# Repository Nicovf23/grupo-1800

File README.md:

# grupo-DON JULIO 
Proyecto Carrito Don Julio
El proyecto Carrito Don Julio consiste en el diseño y desarrollo de un vehículo eléctrico a escala, controlado por radio (RC), orientado al automodelismo de competición en pista para adultos. El objetivo es construir un vehículo desde cero, con un diseño enfocado en el alto rendimiento, la precisión de conducción y las exigencias técnicas de las carreras RC.
El proyecto contempla el diseño y fabricación de un chasis propio, la integración de un sistema de propulsión 100 % eléctrico, el desarrollo de circuitos electrónicos con componentes SMD (Surface-Mount Device) y la implementación de sistemas de control. Cada elemento será diseñado y seleccionado considerando factores como la velocidad, la aceleración, la estabilidad, la distribución del peso y la eficiencia energética.
Para el diseño y desarrollo se utilizarán herramientas especializadas como FreeCAD, para el modelado tridimensional del chasis y sus componentes mecánicos; KiCad, para el diseño de esquemáticos y placas de circuito impreso; Qucs-S, para la simulación y el análisis de circuitos electrónicos; y OpenModelica, para el modelado y la simulación de sistemas dinámicos.
El enfoque principal será desarrollar un vehículo competitivo para carreras en circuitos de pista, aplicando principios de ingeniería mecánica, electrónica, programación y microcontroladores. Se buscará optimizar cada componente para obtener un equilibrio entre potencia, control, estabilidad y rendimiento, mediante un proceso continuo de diseño, fabricación, pruebas y ajustes.

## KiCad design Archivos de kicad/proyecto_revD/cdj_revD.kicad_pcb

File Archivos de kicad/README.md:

# Carrito Don Julio: placa principal (KiCad)

> ⚠️ **ESTADO: EN DESARROLLO. NO ES UNA VERSIÓN DE PRODUCCIÓN.**
> El ruteo está completo (DRC: 0 errores, 0 conexiones sin rutear), pero no mandar a fabricar todavía: faltan verificaciones físicas y una revisión del diseño (ver [AUDITORIA.md](AUDITORIA.md)).

**Revisión:** D, ruteo 3 (11 de noviembre de 2026)
**Herramienta:** KiCad 9.0
**Vehículo:** RC 1:7, 4WD, batería LiPo 6S (22.2 V nominal / 25.2 V cargada)

## Qué hace esta placa

| Bloque | Componentes principales |
|---|---|
| Microcontrolador | ESP32 DevKit V1 (DOIT, 30 pines) en zócalo |
| Sensor de movimiento | IMU LSM6DSL (I2C, dirección 0x6A) |
| Carga de batería por USB-C | CH224K (pide 20 V por PD) → BQ25756 (buck-boost 6S) |
| Monitoreo y balanceo de celdas | BQ76930 (6 celdas, por el cable de balanceo) |
| Alimentación 3.3 V | AP63203WU (componente recomendado por el profesor) |
| Luces | 2× BTS723GW (4 canales con diagnóstico) |
| Radio control | Entradas PWM ×3 + serie (CRSF/SBUS/iBUS), protegidas |
| Salidas | ESC y servo con buffer y habilitación |
| Protección | ESD5Z3.3T, SMF24CA/SMF26CA, SMF3.3, MBRA340T, fusible |

## Estructura de la carpeta

| Carpeta | Contenido |
|---|---|
| `proyecto_revD/` | Proyecto KiCad editable: esquemático, PCB, librería propia `CDJ` (símbolos y huellas) |
| `fabricacion_PRELIMINAR/` | Gerbers, taladros, BOM, posiciones (CPL) y modelo STEP. **Preliminares, no fabricar** |
| `documentacion/` | Esquemático en PDF, vista 3D, BOM clasificada (A/B/C), mapa de pines del DevKit, instrucciones y `EXPLICACION_PLACA.md` (qué hace cada componente y cada parte del PCB) |
| `reportes/` | Informes ERC, DRC y verificación de la netlist |
| `AUDITORIA.md` | Qué está verificado, qué no, y qué falta para producción |
| `NOTAS_DISENO.md` | Decisiones de diseño, supuestos y cálculos |

## Cómo abrir

1. Abrir `proyecto_revD/cdj_revD.kicad_pro` con KiCad 9.
2. La librería `CDJ` se carga sola desde la carpeta del proyecto (`sym-lib-table` y `fp-lib-table`).

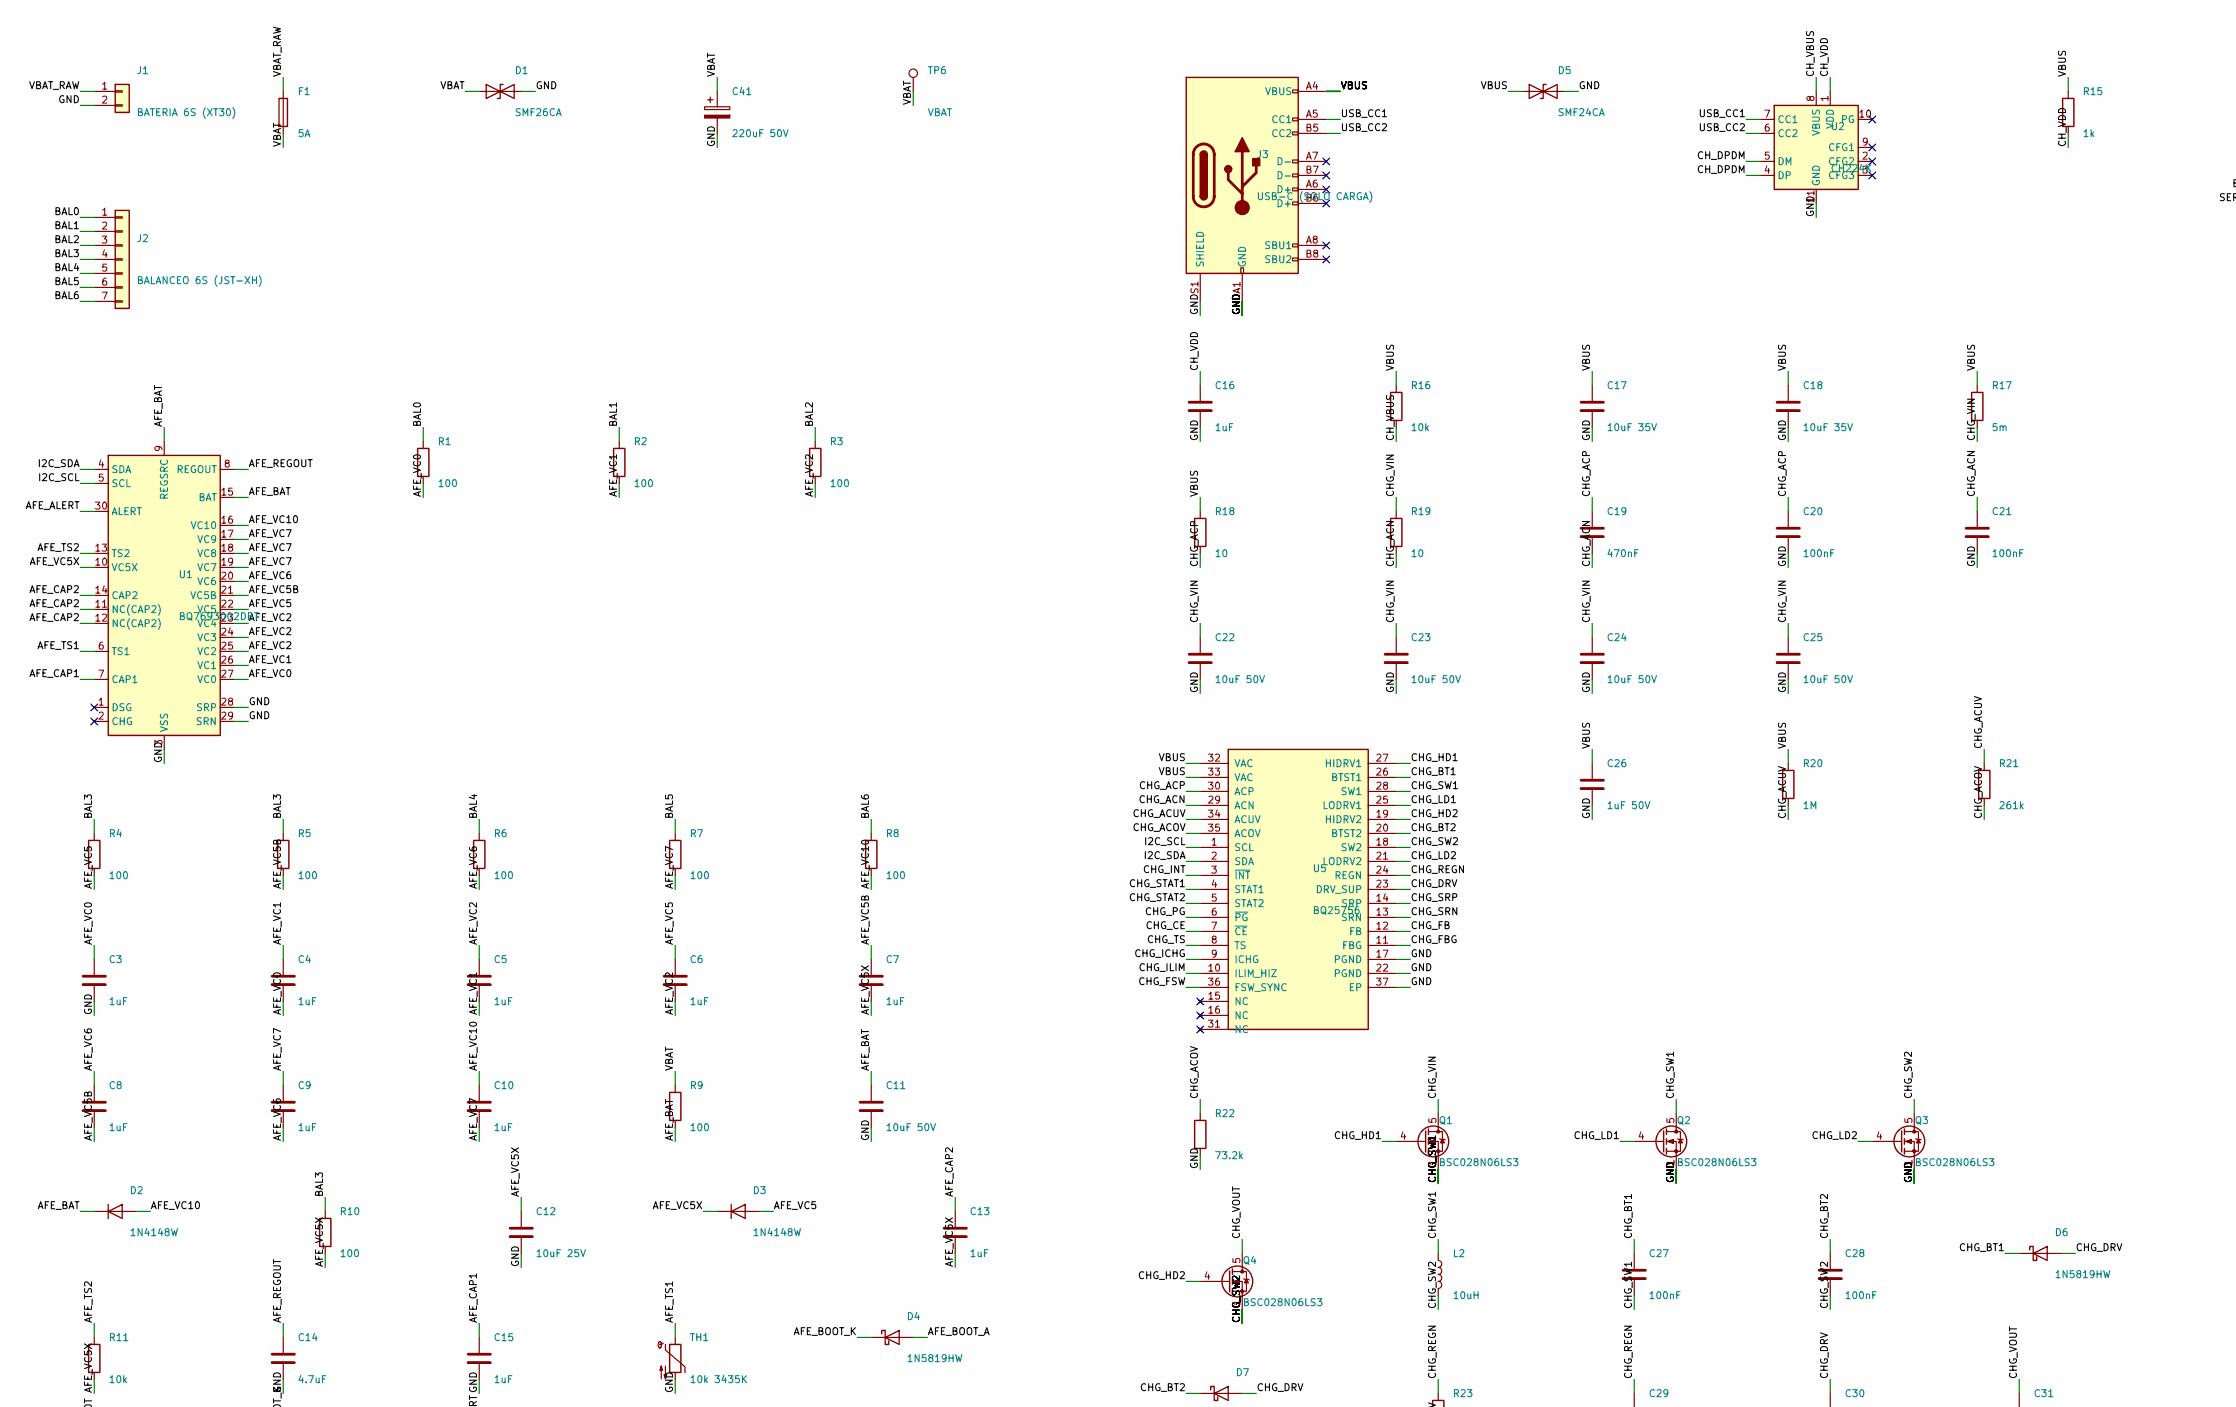
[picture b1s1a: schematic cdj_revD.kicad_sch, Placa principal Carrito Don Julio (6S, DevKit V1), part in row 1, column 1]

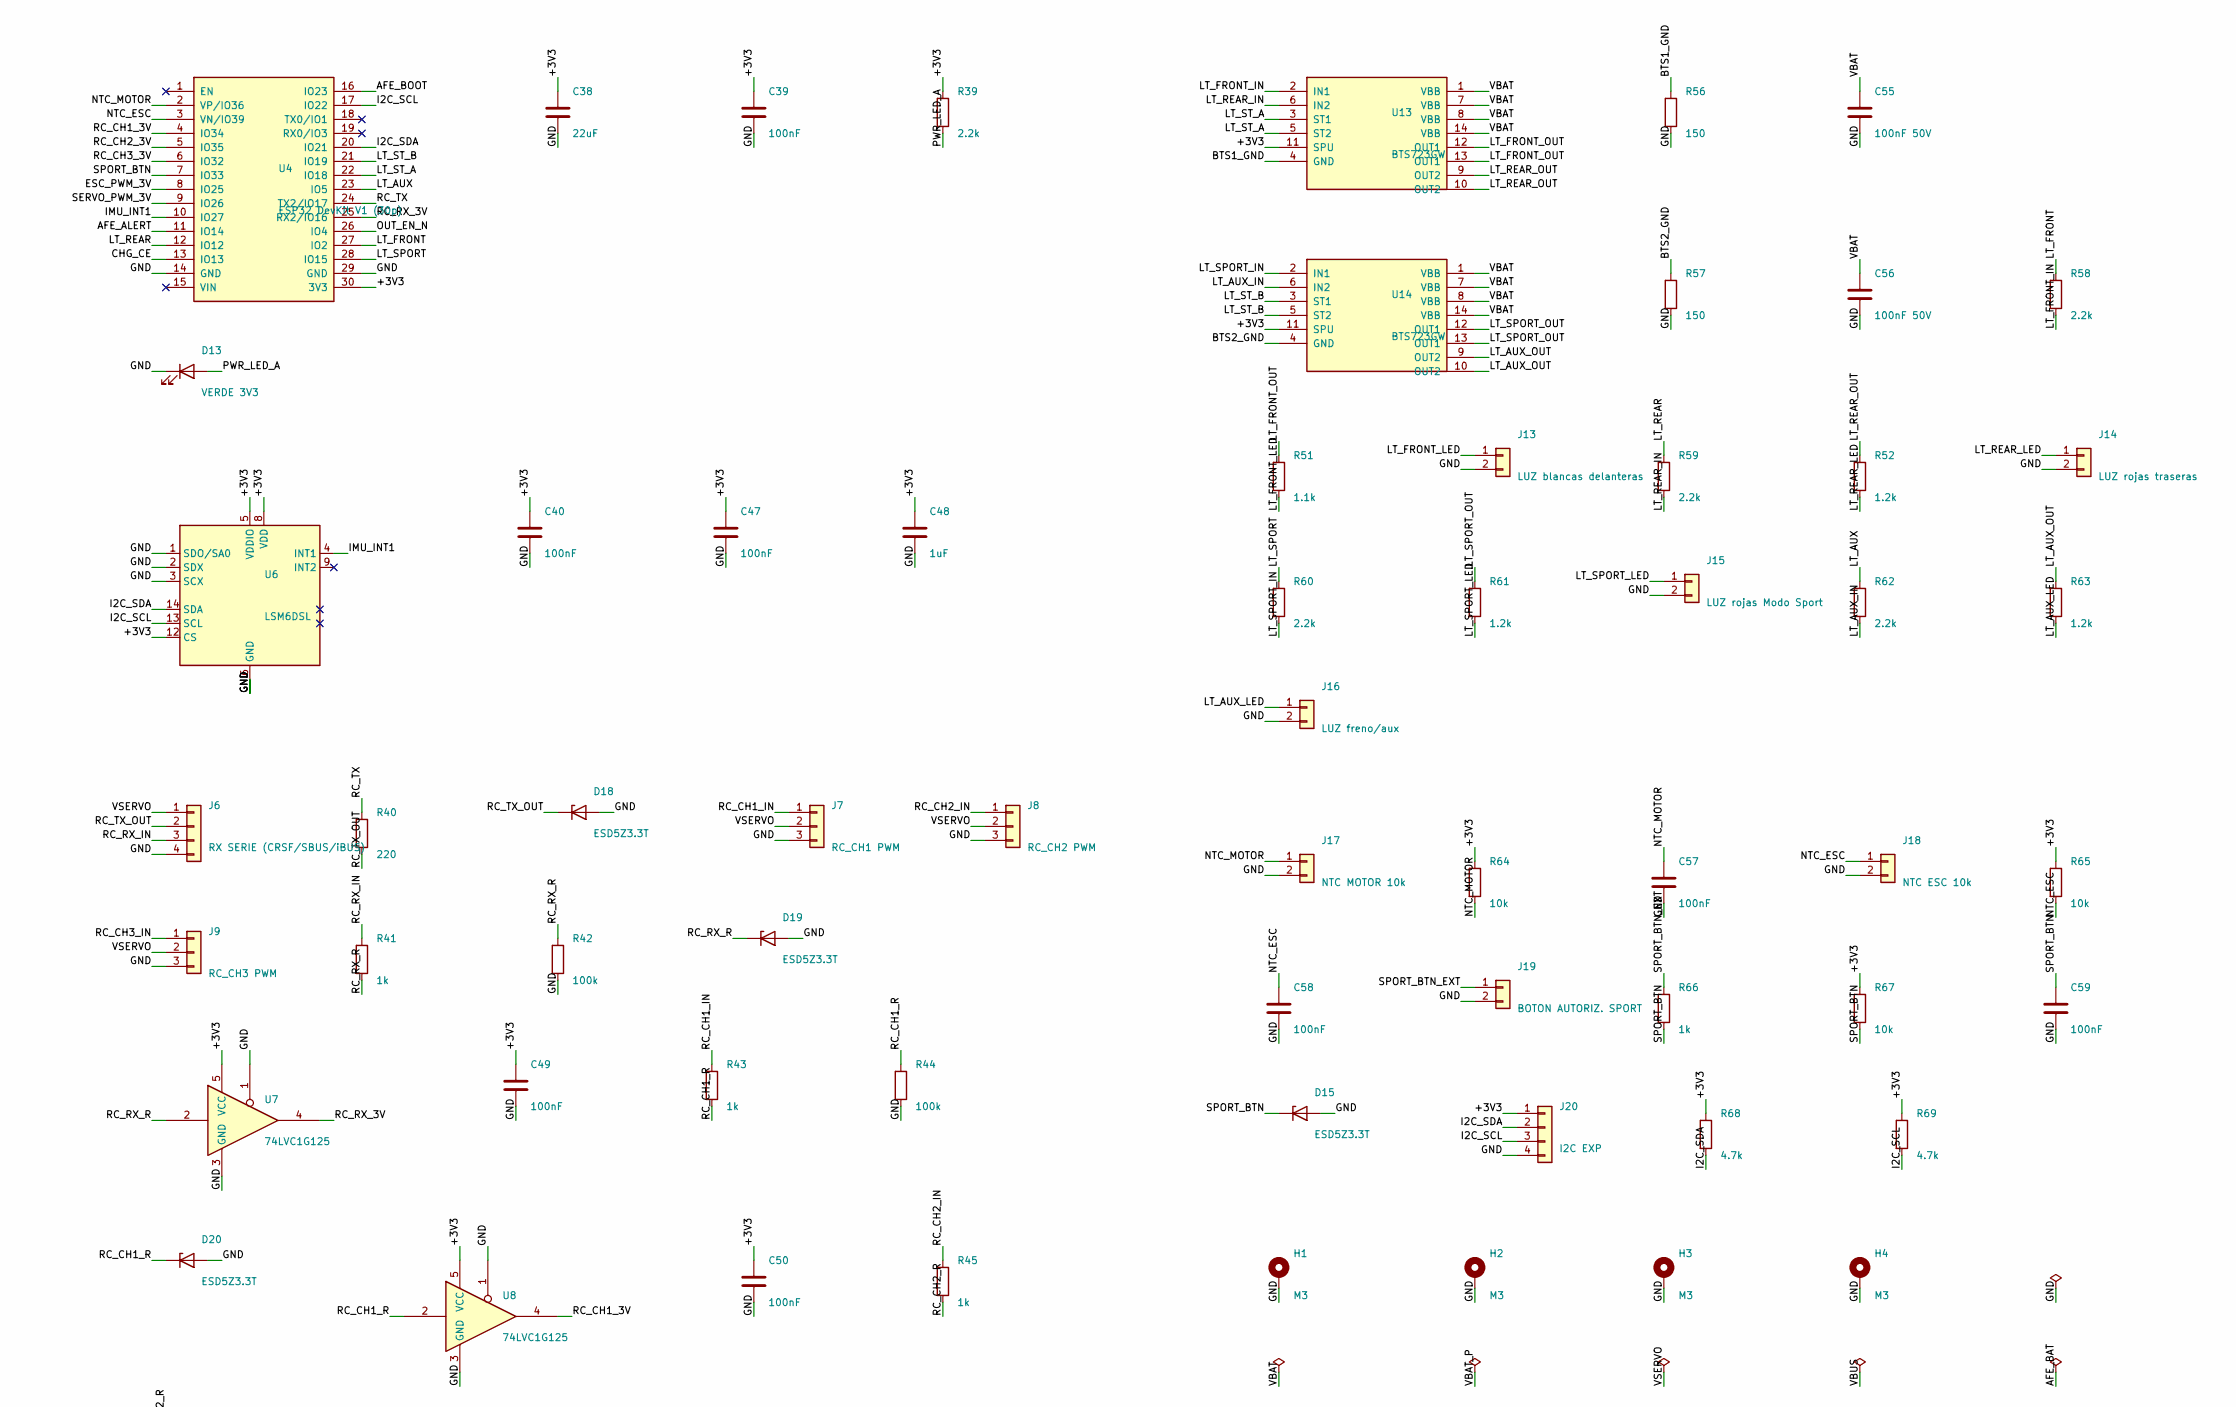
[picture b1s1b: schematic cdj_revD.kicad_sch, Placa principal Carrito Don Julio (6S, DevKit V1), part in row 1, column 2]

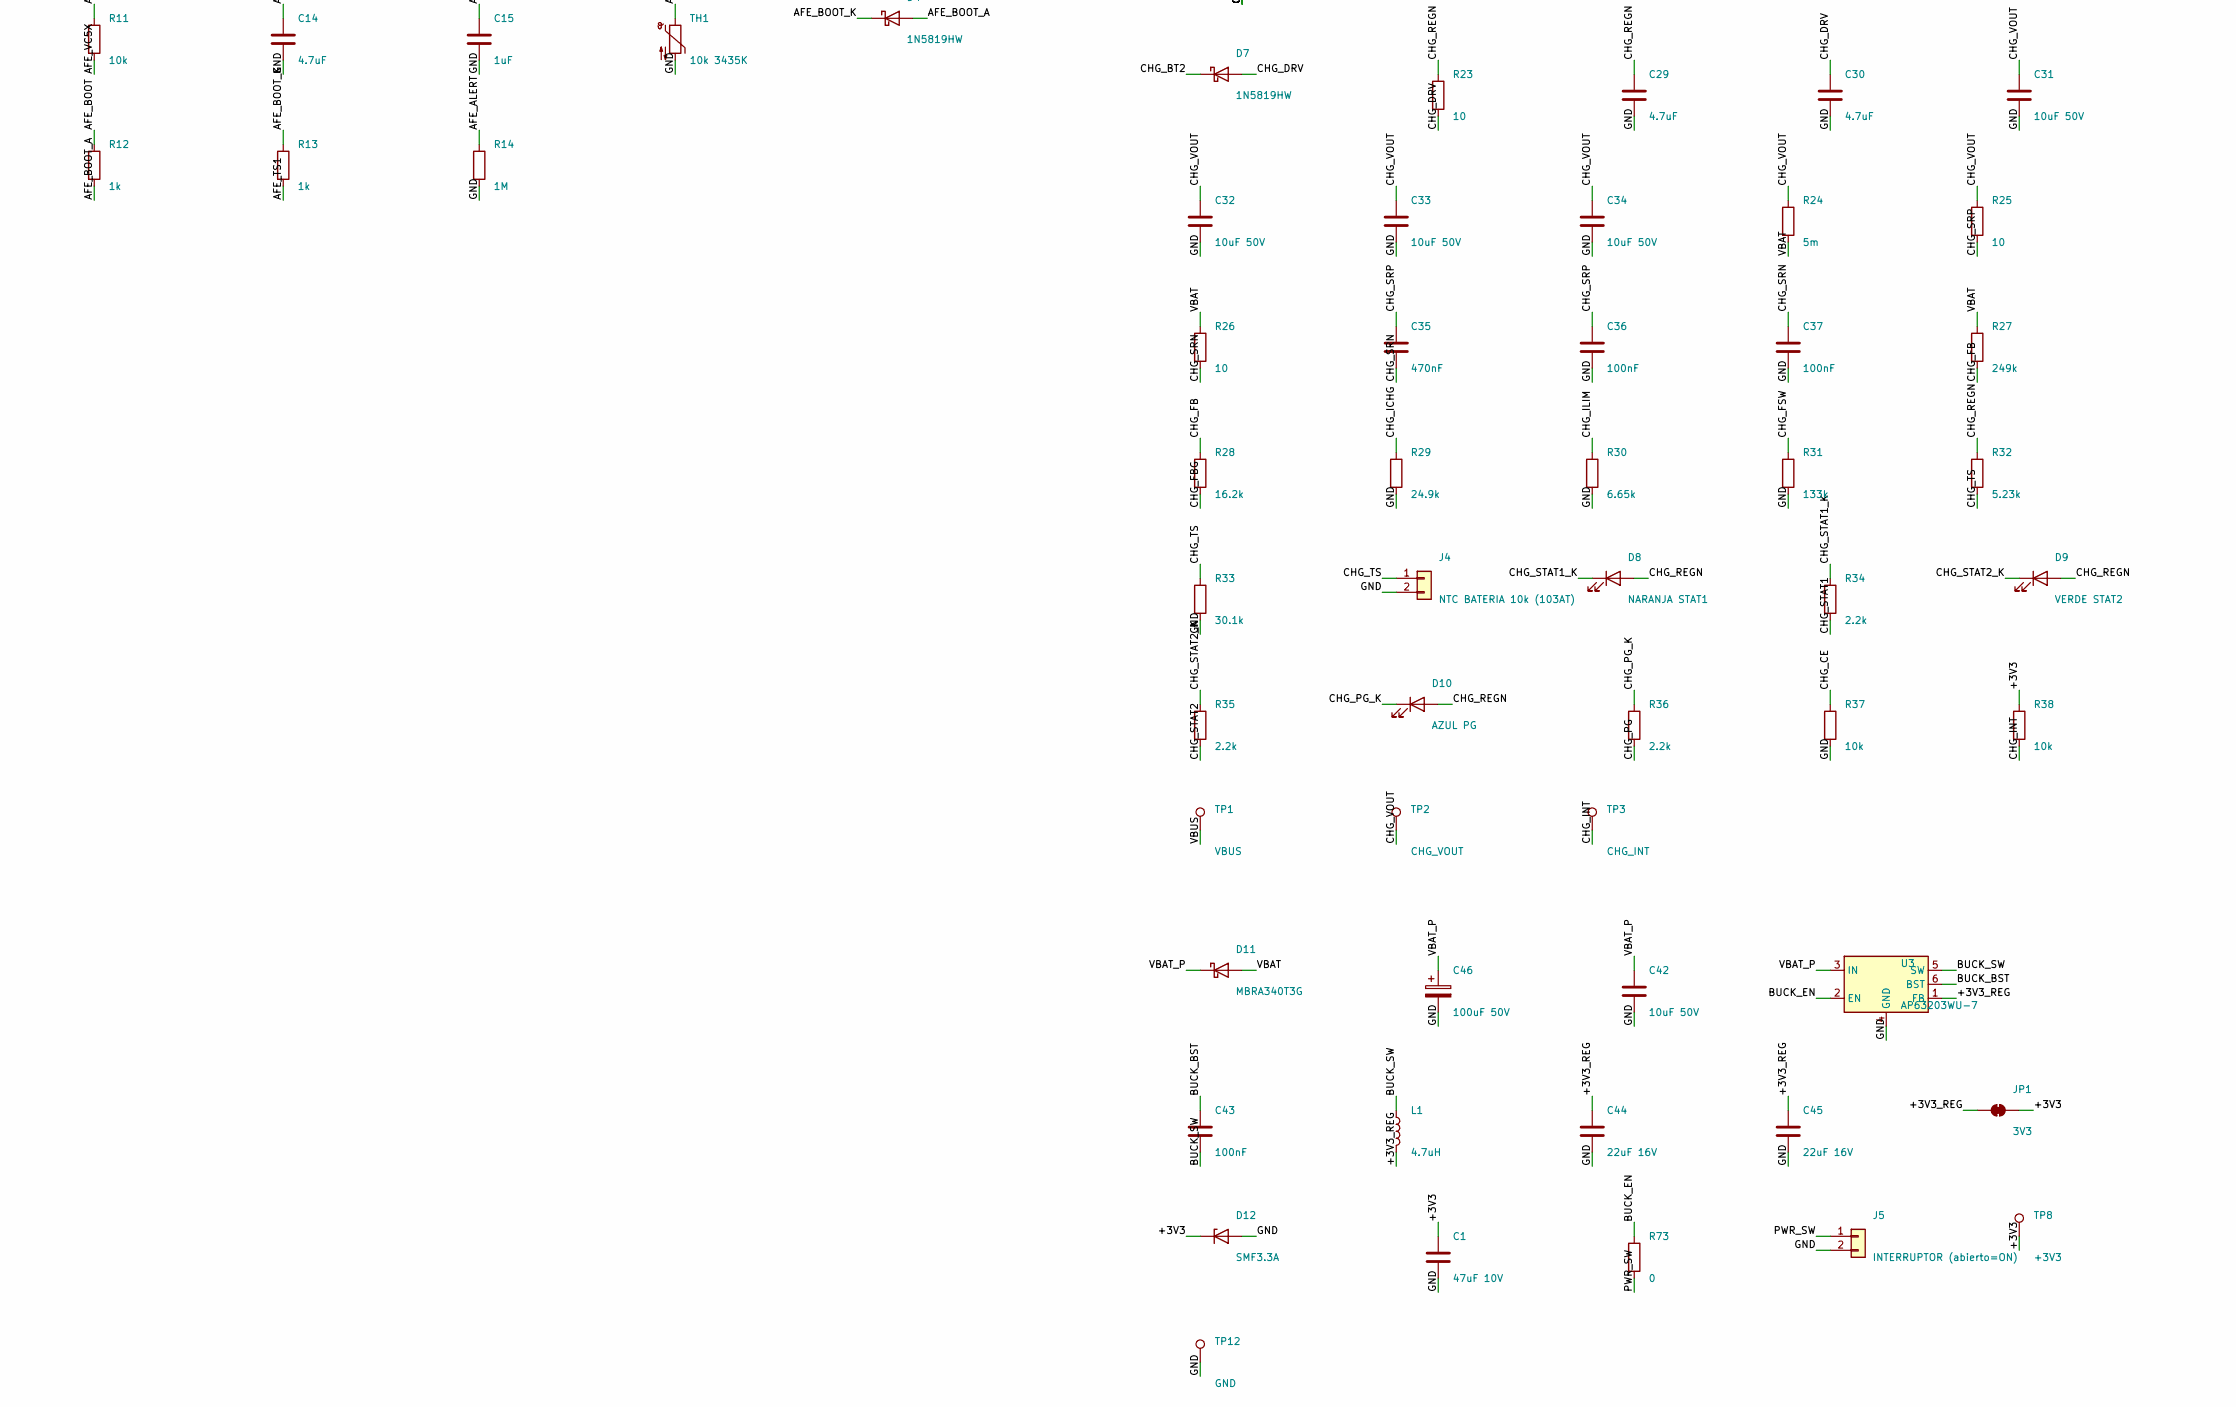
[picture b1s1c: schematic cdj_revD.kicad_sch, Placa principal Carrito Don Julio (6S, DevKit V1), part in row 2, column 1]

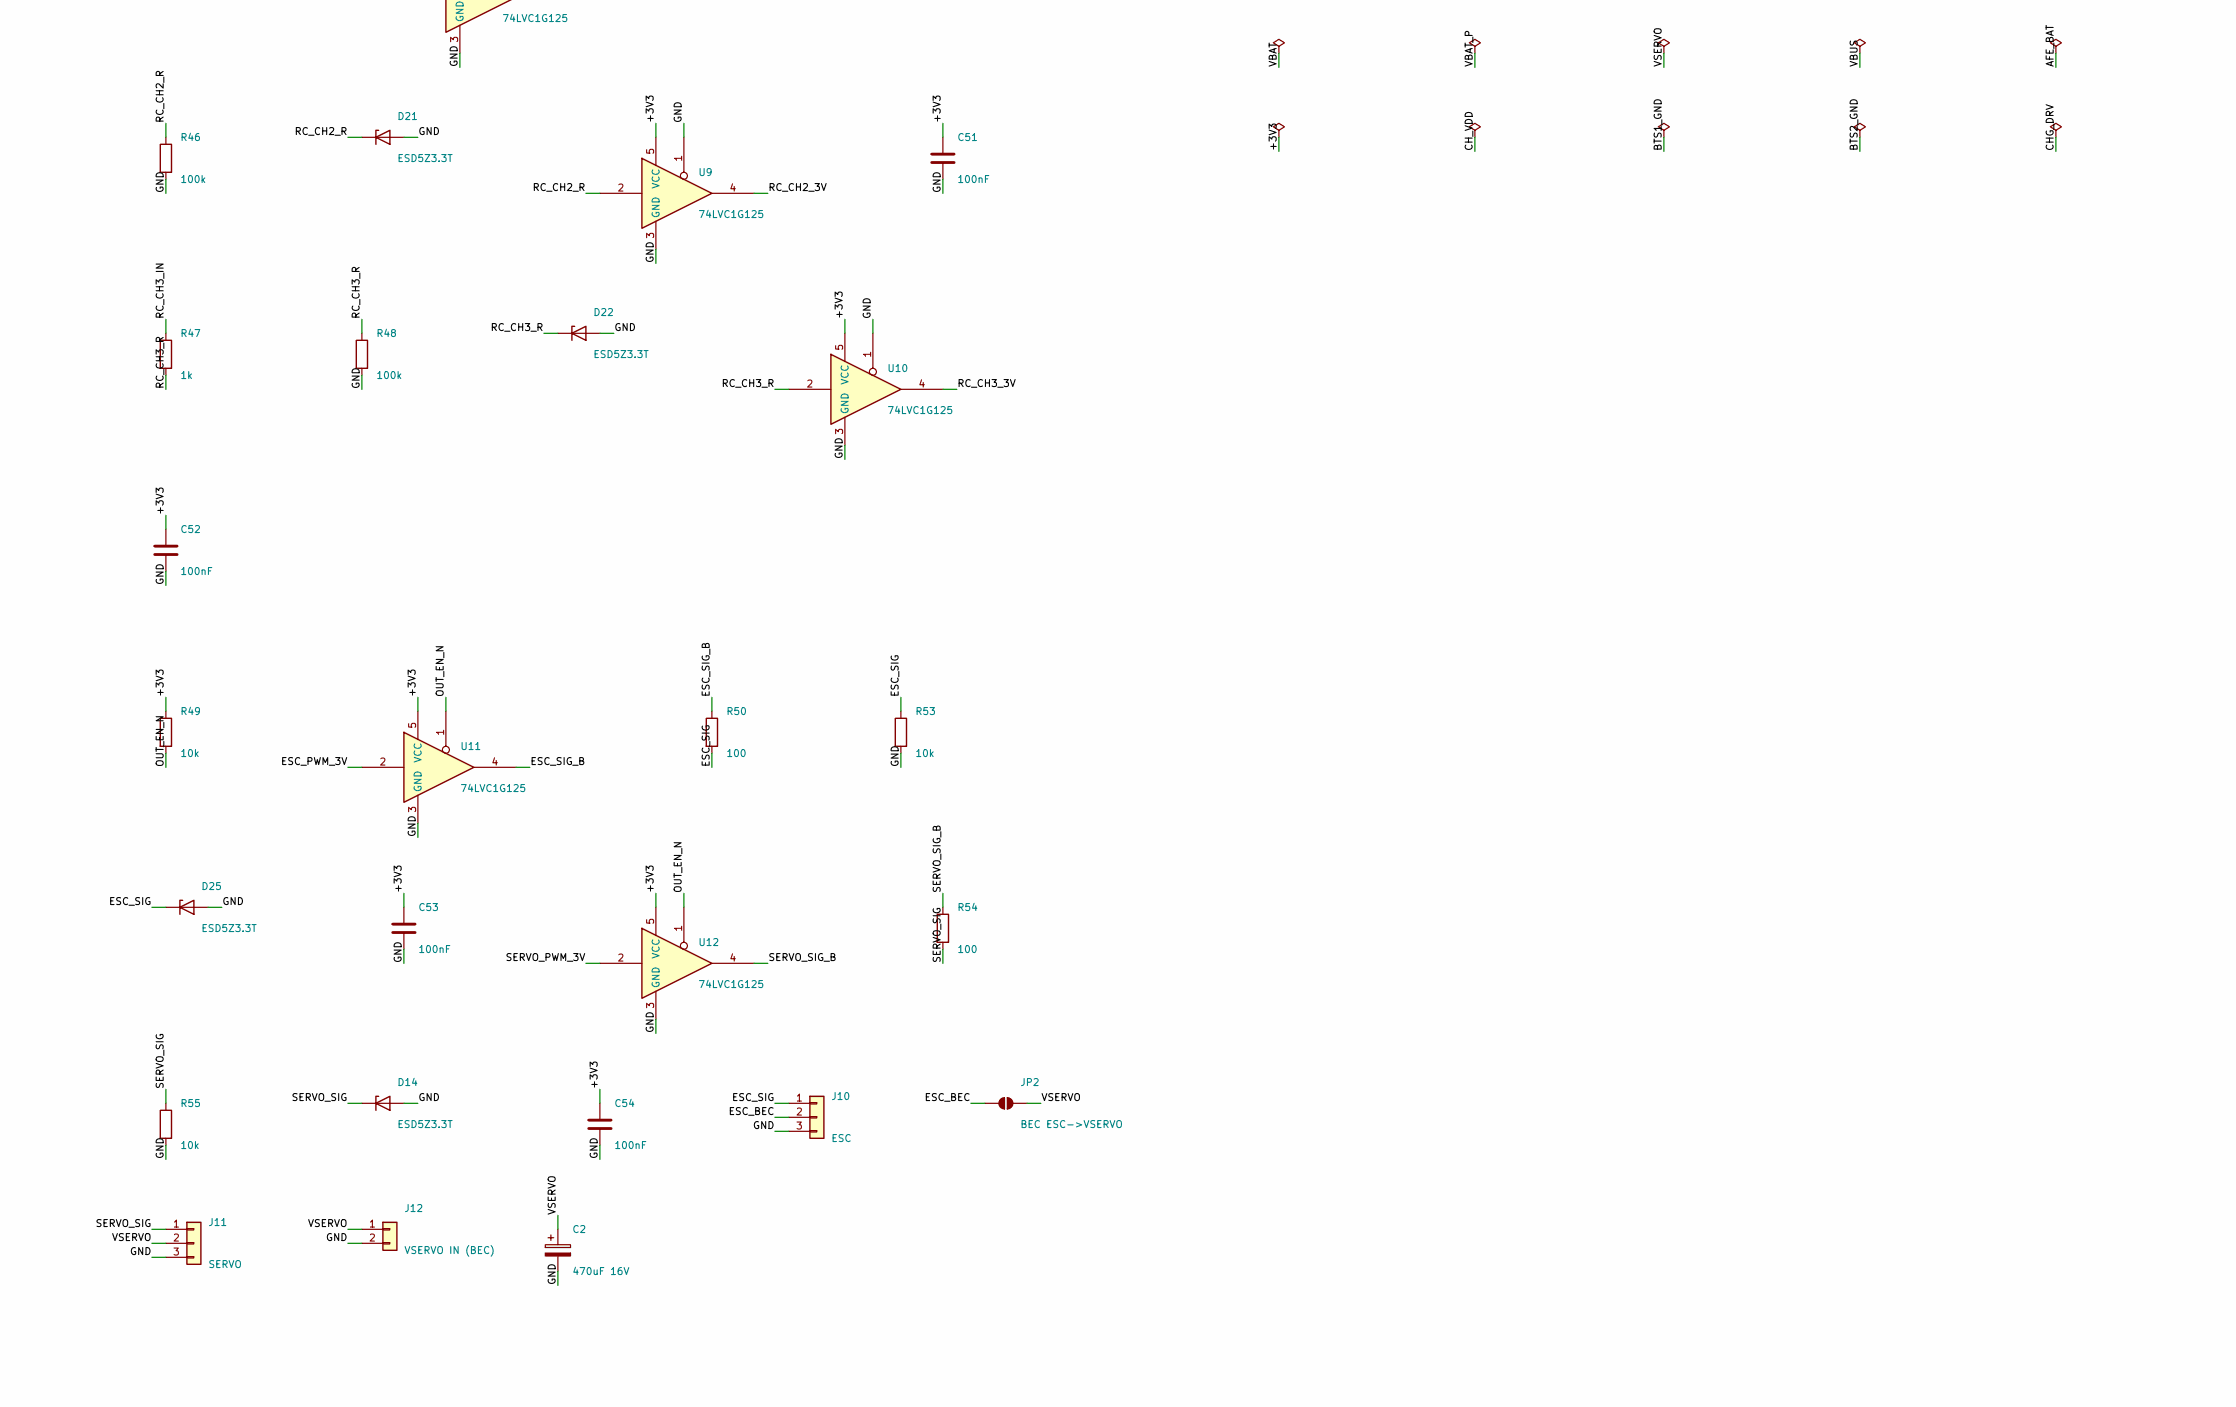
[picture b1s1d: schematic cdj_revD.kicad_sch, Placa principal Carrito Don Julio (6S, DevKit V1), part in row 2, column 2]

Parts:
C1: 47uF 10V; C_1206_3216Metric; MPN X5R 1206 10V
C2: 470uF 16V; CP_Elec_8x10.5; MPN Aluminio 470uF/16V low-ESR
C3, C4, C5, C6, C7, C8, C9, C10, C13: 1uF; C_0603_1608Metric; MPN X7R 0603 25V
C11: 10uF 50V; C_1206_3216Metric; MPN X7R 1206 50V
C12: 10uF 25V; C_0805_2012Metric; MPN X7R 0805 25V
C14: 4.7uF; C_0805_2012Metric; MPN X7R 0805 10V
C15, C16, C48: 1uF; C_0603_1608Metric; MPN X7R 0603
C17, C18: 10uF 35V; C_1206_3216Metric; MPN X5R 1206 35V
C19, C35: 470nF; C_0603_1608Metric; MPN X7R 0603 50V
C20, C21, C36, C37: 100nF; C_0603_1608Metric; MPN X7R 0603 50V
C22, C23, C24, C25, C31, C32, C33, C34, C42: 10uF 50V; C_1206_3216Metric; MPN X5R 1206 50V
C26: 1uF 50V; C_0603_1608Metric; MPN X7R 0603 50V
C27, C28, C43: 100nF; C_0603_1608Metric; MPN X7R 0603 25V
C29, C30: 4.7uF; C_0805_2012Metric; MPN X7R 0805 16V
C38: 22uF; C_0805_2012Metric; MPN X5R 0805 10V
C39, C40, C47, C49, C50, C51, C52, C53, C54, C57, C58, C59: 100nF; C_0603_1608Metric; MPN X7R 0603
C41: 220uF 50V; CP_Elec_10x10.5; MPN Aluminio 220uF/50V
C44, C45: 22uF 16V; C_1206_3216Metric; MPN X5R 1206 16V
C46: 100uF 50V; CP_Elec_8x10.5; MPN Aluminio 100uF/50V
C55, C56: 100nF 50V; C_0603_1608Metric; MPN X7R 0603 50V
D1: SMF26CA; D_SOD-123F; MPN Littelfuse SMF26CA
D2, D3: 1N4148W; D_SOD-123; MPN Diodes 1N4148W-7-F
D4, D6, D7: 1N5819HW; D_SOD-123; MPN Diodes 1N5819HW-7-F
D5: SMF24CA; D_SOD-123F; MPN Littelfuse SMF24CA
D8: NARANJA STAT1; LED_0603_1608Metric; MPN LED 0603
D9: VERDE STAT2; LED_0603_1608Metric; MPN LED 0603
D10: AZUL PG; LED_0603_1608Metric; MPN LED 0603
D11: MBRA340T3G; D_SMA; MPN onsemi MBRA340T3G
D12: SMF3.3A; D_SOD-123F; MPN Littelfuse SMF3.3A (verificar sufijo)
D13: VERDE 3V3; LED_0603_1608Metric; MPN LED verde 0603
D14, D15, D18, D19, D20, D21, D22, D25: ESD5Z3.3T; D_SOD-523; MPN onsemi ESD5Z3.3T1G
F1: 5A; Fuse_Littelfuse-NANO2-451_453; MPN Littelfuse 0451005.MRL (5A, verificar V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
H1, H2, H3, H4: M3; MountingHole_3.2mm_M3_Pad_Via; MPN M3 + arandela antivibracion
J1: BATERIA 6S (XT30); AMASS_XT30PW-M_1x02_P2.50mm_Horizontal; MPN AMASS XT30PW-M
J2: BALANCEO 6S (JST-XH); JST_XH_B7B-XH-A_1x07_P2.50mm_Vertical; MPN JST B7B-XH-A
J3: USB-C (SOLO CARGA); USB_C_Receptacle_HRO_TYPE-C-31-M-12; MPN HRO TYPE-C-31-M-12
J4: NTC BATERIA 10k (103AT); JST_PH_B2B-PH-K_1x02_P2.00mm_Vertical; MPN JST B2B-PH-K-S
J5: INTERRUPTOR (abierto=ON); JST_PH_B2B-PH-K_1x02_P2.00mm_Vertical; MPN JST B2B-PH-K-S
J6: RX SERIE (CRSF/SBUS/iBUS); JST_PH_B4B-PH-K_1x04_P2.00mm_Vertical; MPN JST B4B-PH-K-S
J7: RC_CH1 PWM; PinHeader_1x03_P2.54mm_Vertical; MPN Header 1x03 2.54mm
J8: RC_CH2 PWM; PinHeader_1x03_P2.54mm_Vertical; MPN Header 1x03 2.54mm
J9: RC_CH3 PWM; PinHeader_1x03_P2.54mm_Vertical; MPN Header 1x03 2.54mm
J10: ESC; PinHeader_1x03_P2.54mm_Vertical; MPN Header 1x03 2.54mm
J11: SERVO; PinHeader_1x03_P2.54mm_Vertical; MPN Header 1x03 2.54mm
J12: VSERVO IN (BEC); AMASS_XT30PW-M_1x02_P2.50mm_Horizontal; MPN AMASS XT30PW-M
J13: LUZ blancas delanteras; JST_PH_B2B-PH-K_1x02_P2.00mm_Vertical; MPN JST B2B-PH-K-S
J14: LUZ rojas traseras; JST_PH_B2B-PH-K_1x02_P2.00mm_Vertical; MPN JST B2B-PH-K-S
J15: LUZ rojas Modo Sport; JST_PH_B2B-PH-K_1x02_P2.00mm_Vertical; MPN JST B2B-PH-K-S
J16: LUZ freno/aux; JST_PH_B2B-PH-K_1x02_P2.00mm_Vertical; MPN JST B2B-PH-K-S
J17: NTC MOTOR 10k; JST_PH_B2B-PH-K_1x02_P2.00mm_Vertical; MPN JST B2B-PH-K-S
J18: NTC ESC 10k; JST_PH_B2B-PH-K_1x02_P2.00mm_Vertical; MPN JST B2B-PH-K-S
J19: BOTON AUTORIZ. SPORT; JST_PH_B2B-PH-K_1x02_P2.00mm_Vertical; MPN JST B2B-PH-K-S
J20: I2C EXP; JST_PH_B4B-PH-K_1x04_P2.00mm_Vertical; MPN JST B4B-PH-K-S
JP1: 3V3; SolderJumper-2_P1.3mm_Bridged_RoundedPad1.0x1.5mm; MPN Puente soldadura (cerrado)
JP2: BEC ESC->VSERVO; SolderJumper-2_P1.3mm_Open_RoundedPad1.0x1.5mm; MPN Puente soldadura (abierto)
L1: 4.7uH; L_APV_APH0630; MPN APV APH0630T4R7M (4.7uH, Isat 8-9A, DCR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
L2: 10uH; L_Vishay_IHLP-4040; MPN Vishay IHLP4040DZER100M5A (LCSC C511353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
Q1, Q2, Q3, Q4: BSC028N06LS3; TDSON-8-1; MPN Infineon BSC028N06LS3 (60V 2.8mOhm, log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
R1, R2, R3, R4, R5, R6, R7, R8, R9, R10, R50, R54: 100; R_0603_1608Metric; MPN 1% 0603
R11, R16, R37, R38, R49, R53, R55, R64, R65, R67: 10k; R_0603_1608Metric; MPN 1% 0603
R12, R13, R15, R41, R43, R45, R47, R66: 1k; R_0603_1608Metric; MPN 1% 0603
R14, R20: 1M; R_0603_1608Metric; MPN 1% 0603
R17, R24: 5m; R_1206_3216Metric; MPN Shunt 5mOhm 1206 1W
R18, R19, R23, R25, R26: 10; R_0603_1608Metric; MPN 1% 0603
R21: 261k; R_0603_1608Metric; MPN 1% 0603
R22: 73.2k; R_0603_1608Metric; MPN 1% 0603
R27: 249k; R_0603_1608Metric; MPN 1% 0603
R28: 16.2k; R_0603_1608Metric; MPN 1% 0603
R29: 24.9k; R_0603_1608Metric; MPN 1% 0603
R30: 6.65k; R_0603_1608Metric; MPN 1% 0603
R31: 133k; R_0603_1608Metric; MPN 1% 0603
R32: 5.23k; R_0603_1608Metric; MPN 1% 0603
R33: 30.1k; R_0603_1608Metric; MPN 1% 0603
R34, R35, R36, R39, R58, R59, R60, R62: 2.2k; R_0603_1608Metric; MPN 1% 0603
R40: 220; R_0603_1608Metric; MPN 1% 0603
R42, R44, R46, R48: 100k; R_0603_1608Metric; MPN 1% 0603
R51: 1.1k; R_2512_6332Metric; MPN 2512 1W (1 LED a 6S: 0.45W; 0R si el mo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
R52, R61, R63: 1.2k; R_2512_6332Metric; MPN 2512 1W (1 LED a 6S: 0.45W; 0R si el mo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
R56, R57: 150; R_0603_1608Metric; MPN 1% 0603
R68, R69: 4.7k; R_0603_1608Metric; MPN 1% 0603
R73: 0; R_0603_1608Metric; MPN 1% 0603
TH1: 10k 3435K; R_0603_1608Metric; MPN Murata NCP18XH103F03RB
TP1: VBUS; TestPoint_Pad_D1.5mm; MPN Pad de prueba
TP2: CHG_VOUT; TestPoint_Pad_D1.5mm; MPN Pad de prueba
TP3: CHG_INT; TestPoint_Pad_D1.5mm; MPN Pad de prueba
TP6: VBAT; TestPoint_Pad_D1.5mm; MPN Pad de prueba
TP8: +3V3; TestPoint_Pad_D1.5mm; MPN Pad de prueba
TP12: GND; TestPoint_Pad_D1.5mm; MPN Pad de prueba
U1: BQ7693002DBT; TSSOP-30_4.4x7.8mm_P0.5mm; MPN TI BQ7693002DBTR (REGOUT 3.3V, I2C 0x08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
U2: CH224K; SSOP-10-1EP_3.9x4.9mm_P1mm_EP2.1x3.3mm; MPN WCH CH224K (LCSC C970725)
U3: AP63203WU-7; TSOT-23-6; MPN Diodes AP63203WU-7
U4: ESP32 DevKit V1 (30p); ESP32_DevKit_V1_30P; MPN DOIT ESP32 DevKit V1 30 pines + 2x tira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
U5: BQ25756; QFN-36-1EP_5x6mm_P0.5mm_EP3.6x4.6mm; MPN TI BQ25756RRVR (LCSC C19272232)
U6: LSM6DSL; LGA-14_3x2.5mm_P0.5mm_LayoutBorder3x4y; MPN ST LSM6DSLTR
U7, U8, U9, U10, U11, U12: 74LVC1G125; SOT-23-5; MPN TI SN74LVC1G125DBVR
U13, U14: BTS723GW; SOIC-14_3.9x8.7mm_P1.27mm; MPN Infineon BTS723GWXUMA1

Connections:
/+3V3: C1.1, C38.1, C39.1, C40.1, C47.1, C48.1, C49.1, C50.1, C51.1, C52.1, C53.1, C54.1, D12.1 (K), J20.1, JP1.2 (B), R38.1, R39.1, R49.1, R64.1, R65.1, R67.1, R68.1, R69.1, TP8.1, U4.30 (3V3), U6.5 (VDDIO), U6.8 (VDD), U6.12 (CS), U7.5 (VCC), U8.5 (VCC), U9.5 (VCC), U10.5 (VCC), U11.5 (VCC), U12.5 (VCC), U13.11 (SPU), U14.11 (SPU)
/+3V3_REG: C44.1, C45.1, JP1.1 (A), L1.2, U3.1 (FB)
/AFE_ALERT: R14.1, U1.30 (ALERT), U4.11 (IO14)
/AFE_BAT: C11.1, D2.1 (K), R9.2, U1.9 (REGSRC), U1.15 (BAT)
/AFE_BOOT: R12.1, U4.16 (IO23)
/AFE_BOOT_A: D4.2 (A), R12.2
/AFE_BOOT_K: D4.1 (K), R13.1
/AFE_CAP1: C15.1, U1.7 (CAP1)
/AFE_CAP2: C13.1, U1.11 (NC(CAP2)), U1.12 (NC(CAP2)), U1.14 (CAP2)
/AFE_REGOUT: C14.1, U1.8 (REGOUT)
/AFE_TS1: R13.2, TH1.1, U1.6 (TS1)
/AFE_TS2: R11.1, U1.13 (TS2)
/AFE_VC0: C3.1, C4.2, R1.2, U1.27 (VC0)
/AFE_VC1: C4.1, C5.2, R2.2, U1.26 (VC1)
/AFE_VC2: C5.1, C6.2, R3.2, U1.23 (VC4), U1.24 (VC3), U1.25 (VC2)
/AFE_VC5: C6.1, D3.2 (A), R4.2, U1.22 (VC5)
/AFE_VC5B: C7.1, C8.2, R5.2, U1.21 (VC5B)
/AFE_VC5X: C7.2, C12.1, C13.2, D3.1 (K), R10.2, R11.2, U1.10 (VC5X)
/AFE_VC6: C8.1, C9.2, R6.2, U1.20 (VC6)
/AFE_VC7: C9.1, C10.2, R7.2, U1.17 (VC9), U1.18 (VC8), U1.19 (VC7)
/AFE_VC10: C10.1, D2.2 (A), R8.2, U1.16 (VC10)
/BAL0: J2.1, R1.1
/BAL1: J2.2, R2.1
/BAL2: J2.3, R3.1
/BAL3: J2.4, R4.1, R5.1, R10.1
/BAL4: J2.5, R6.1
/BAL5: J2.6, R7.1
/BAL6: J2.7, R8.1
/BTS1_GND: R56.1, U13.4 (GND)
/BTS2_GND: R57.1, U14.4 (GND)
/BUCK_BST: C43.1, U3.6 (BST)
/BUCK_EN: R73.1, U3.2 (EN)
/BUCK_SW: C43.2, L1.1, U3.5 (SW)
/CHG_ACN: C19.2, C21.1, R19.2, U5.29 (ACN)
/CHG_ACOV: R21.2, R22.1, U5.35 (ACOV)
/CHG_ACP: C19.1, C20.1, R18.2, U5.30 (ACP)
/CHG_ACUV: R20.2, R21.1, U5.34 (ACUV)
/CHG_BT1: C27.1, D6.1 (K), U5.26 (BTST1)
/CHG_BT2: C28.1, D7.1 (K), U5.20 (BTST2)
/CHG_CE: R37.1, U4.13 (IO13), U5.7 (~CE)
/CHG_DRV: C30.1, D6.2 (A), D7.2 (A), R23.2, U5.23 (DRV_SUP)
/CHG_FB: R27.2, R28.1, U5.12 (FB)
/CHG_FBG: R28.2, U5.11 (FBG)
/CHG_FSW: R31.1, U5.36 (FSW_SYNC)
/CHG_HD1: Q1.4 (G), U5.27 (HIDRV1)
/CHG_HD2: Q4.4 (G), U5.19 (HIDRV2)
/CHG_ICHG: R29.1, U5.9 (ICHG)
/CHG_ILIM: R30.1, U5.10 (ILIM_HIZ)
/CHG_INT: R38.2, TP3.1, U5.3 (~INT)
/CHG_LD1: Q2.4 (G), U5.25 (LODRV1)
/CHG_LD2: Q3.4 (G), U5.21 (LODRV2)
/CHG_PG: R36.2, U5.6 (~PG)
/CHG_PG_K: D10.1 (K), R36.1
/CHG_REGN: C29.1, D8.2 (A), D9.2 (A), D10.2 (A), R23.1, R32.1, U5.24 (REGN)
/CHG_SRN: C35.2, C37.1, R26.2, U5.13 (SRN)
/CHG_SRP: C35.1, C36.1, R25.2, U5.14 (SRP)
/CHG_STAT1: R34.2, U5.4 (STAT1)
/CHG_STAT1_K: D8.1 (K), R34.1
/CHG_STAT2: R35.2, U5.5 (STAT2)
/CHG_STAT2_K: D9.1 (K), R35.1
/CHG_SW1: C27.2, L2.1, Q1.1 (S), Q1.2 (S), Q1.3 (S), Q2.5 (D), U5.28 (SW1)
/CHG_SW2: C28.2, L2.2, Q3.5 (D), Q4.1 (S), Q4.2 (S), Q4.3 (S), U5.18 (SW2)
/CHG_TS: J4.1, R32.2, R33.1, U5.8 (TS)
/CHG_VIN: C22.1, C23.1, C24.1, C25.1, Q1.5 (D), R17.2, R19.1
/CHG_VOUT: C31.1, C32.1, C33.1, C34.1, Q4.5 (D), R24.1, R25.1, TP2.1
/CH_DPDM: U2.4 (DP), U2.5 (DM)
/CH_VBUS: R16.2, U2.8 (VBUS)
/CH_VDD: C16.1, R15.2, U2.1 (VDD)
/ESC_BEC: J10.2, JP2.1 (A)
/ESC_PWM_3V: U4.8 (IO25), U11.2
/ESC_SIG: D25.1 (K), J10.1, R50.2, R53.1
/ESC_SIG_B: R50.1, U11.4
/GND: C1.2, C2.2, C3.2, C11.2, C12.2, C14.2, C15.2, C16.2, C17.2, C18.2, C20.2, C21.2, C22.2, C23.2, C24.2, C25.2, C26.2, C29.2, C30.2, C31.2, C32.2, C33.2, C34.2, C36.2, C37.2, C38.2, C39.2, C40.2, C41.2, C42.2, C44.2, C45.2, C46.2, C47.2, C48.2, C49.2, C50.2, C51.2, C52.2, C53.2, C54.2, C55.2, C56.2, C57.2, C58.2, C59.2, D1.2 (A2), D5.2 (A2), D12.2 (A), D13.1 (K), D14.2 (A), D15.2 (A), D18.2 (A), D19.2 (A), D20.2 (A), D21.2 (A), D22.2 (A), D25.2 (A), H1.1, H2.1, H3.1, H4.1, J1.2, J3.A1 (GND), J3.A12 (GND), J3.B1 (GND), J3.B12 (GND), J3.S1 (SHIELD), J4.2, J5.2, J6.4, J7.3, J8.3, J9.3, J10.3, J11.3, J12.2, J13.2, J14.2, J15.2, J16.2, J17.2, J18.2, J19.2, J20.4, Q2.1 (S), Q2.2 (S), Q2.3 (S), Q3.1 (S), Q3.2 (S), Q3.3 (S), R14.2, R22.2, R29.2, R30.2, R31.2, R33.2, R37.2, R42.2, R44.2, R46.2, R48.2, R53.2, R55.2, R56.2, R57.2, TH1.2, TP12.1, U1.3 (VSS), U1.28 (SRP), U1.29 (SRN), U2.11 (GND), U3.4 (GND), U4.14 (GND), U4.29 (GND), U5.17 (PGND), U5.22 (PGND), U5.37 (EP), U6.1 (SDO/SA0), U6.2 (SDX), U6.3 (SCX), U6.6 (GND), U6.7 (GND), U7.1, U7.3 (GND), U8.1, U8.3 (GND), U9.1, U9.3 (GND), U10.1, U10.3 (GND), U11.3 (GND), U12.3 (GND)
/I2C_SCL: J20.3, R69.2, U1.5 (SCL), U4.17 (IO22), U5.1 (SCL), U6.13 (SCL)
/I2C_SDA: J20.2, R68.2, U1.4 (SDA), U4.20 (IO21), U5.2 (SDA), U6.14 (SDA)
/IMU_INT1: U4.10 (IO27), U6.4 (INT1)
/LT_AUX: R62.1, U4.23 (IO5)
/LT_AUX_IN: R62.2, U14.6 (IN2)
/LT_AUX_LED: J16.1, R63.2
/LT_AUX_OUT: R63.1, U14.9 (OUT2), U14.10 (OUT2)
/LT_FRONT: R58.1, U4.27 (IO2)
/LT_FRONT_IN: R58.2, U13.2 (IN1)
/LT_FRONT_LED: J13.1, R51.2
/LT_FRONT_OUT: R51.1, U13.12 (OUT1), U13.13 (OUT1)
/LT_REAR: R59.1, U4.12 (IO12)
/LT_REAR_IN: R59.2, U13.6 (IN2)
/LT_REAR_LED: J14.1, R52.2
/LT_REAR_OUT: R52.1, U13.9 (OUT2), U13.10 (OUT2)
/LT_SPORT: R60.1, U4.28 (IO15)
/LT_SPORT_IN: R60.2, U14.2 (IN1)
/LT_SPORT_LED: J15.1, R61.2
/LT_SPORT_OUT: R61.1, U14.12 (OUT1), U14.13 (OUT1)
/LT_ST_A: U4.22 (IO18), U13.3 (ST1), U13.5 (ST2)
/LT_ST_B: U4.21 (IO19), U14.3 (ST1), U14.5 (ST2)
/NTC_ESC: C58.1, J18.1, R65.2, U4.3 (VN/IO39)
/NTC_MOTOR: C57.1, J17.1, R64.2, U4.2 (VP/IO36)
/OUT_EN_N: R49.2, U4.26 (IO4), U11.1, U12.1
/PWR_LED_A: D13.2 (A), R39.2
/PWR_SW: J5.1, R73.2
/RC_CH1_3V: U4.4 (IO34), U8.4
/RC_CH1_IN: J7.1, R43.1
/RC_CH1_R: D20.1 (K), R43.2, R44.1, U8.2
/RC_CH2_3V: U4.5 (IO35), U9.4
/RC_CH2_IN: J8.1, R45.1
/RC_CH2_R: D21.1 (K), R45.2, R46.1, U9.2
/RC_CH3_3V: U4.6 (IO32), U10.4
/RC_CH3_IN: J9.1, R47.1
/RC_CH3_R: D22.1 (K), R47.2, R48.1, U10.2
/RC_RX_3V: U4.25 (RX2/IO16), U7.4
/RC_RX_IN: J6.3, R41.1
/RC_RX_R: D19.1 (K), R41.2, R42.1, U7.2
/RC_TX: R40.1, U4.24 (TX2/IO17)
/RC_TX_OUT: D18.1 (K), J6.2, R40.2
/SERVO_PWM_3V: U4.9 (IO26), U12.2
/SERVO_SIG: D14.1 (K), J11.1, R54.2, R55.1
/SERVO_SIG_B: R54.1, U12.4
/SPORT_BTN: C59.1, D15.1 (K), R66.2, R67.2, U4.7 (IO33)
/SPORT_BTN_EXT: J19.1, R66.1
/USB_CC1: J3.A5 (CC1), U2.7 (CC1)
/USB_CC2: J3.B5 (CC2), U2.6 (CC2)
/VBAT: C41.1, C55.1, C56.1, D1.1 (A1), D11.2 (A), F1.2, R9.1, R24.2, R26.1, R27.1, TP6.1, U13.1 (VBB), U13.7 (VBB), U13.8 (VBB), U13.14 (VBB), U14.1 (VBB), U14.7 (VBB), U14.8 (VBB), U14.14 (VBB)
/VBAT_P: C42.1, C46.1, D11.1 (K), U3.3 (IN)
/VBAT_RAW: F1.1, J1.1
/VBUS: C17.1, C18.1, C26.1, D5.1 (A1), J3.A4 (VBUS), J3.A9 (VBUS), J3.B4 (VBUS), J3.B9 (VBUS), R15.1, R16.1, R17.1, R18.1, R20.1, TP1.1, U5.32 (VAC), U5.33 (VAC)
/VSERVO: C2.1, J6.1, J7.2, J8.2, J9.2, J11.2, J12.1, JP2.2 (B)
